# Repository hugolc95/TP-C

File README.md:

#Hugo LE COZ 3DN 

USART2 mode asynchrone baud rate = 115200 bit/s

Clock configuration = 32 MHz 

## **1.2 Le microcontrôleur sous KiCAD**

13. PB9 à la masse permet de choisir la selection du modes de boot

14. Le role de L1, C5, C7 est un filtre passe bas du second ordre qui permet de supprimer les parasites de l'alimentation

## **1.3 Le reste du schémas**

3. On peut retrouver sur la première page la valeur que doit avoir au minimum Cin et Cout de 0.47uF mais sur la page 3 on nous indique une valeur typique de 1uF
4.
5. Valeur condensateur page 25
6. CS => Chip Select est activée à l'état bas et permettre ainsi l'établissement de la communication SPI
7. LDAC => (Load DAC) Lorsque cette entrée est à 0, elle provoque un changement de la tension de sortie et lorsque la broche LDAC est activée, les valeurs enregistrées dans le registre de mise à jour sont chargées simultanément dans tous les DAC associés. Cela permet d'assurer une mise à jour cohérente et synchrone des sorties analogiques.
8. MISO => la broche MISO n'existe pas dans le DAC
9.
10. cela se trouve dans la documentation du STLink page 26

## **3.1 Activation des LL drivers**

2. 
3.
4. __STATIC_INLINE est un modificateur de type de fonction qui indique au compilateur de traiter la fonction comme étant statique et en ligne.
5.

##3.2 LED simple

2. La valeur du prescaler est de 63

## 3.3 LED avec timer

1- On active le TIM21 

2- Pour qu'il y est des interruption toutes les milli-secondes
On met 16000 pour le prescaler et 1000 pour l'AutoReloadRegister (ARR)

6- La routine de service d’interruption se trouve dans le fichier stm3210xx_it.c

7- 

## 3.4 UART

code photo telephone

5- il manque le **&**, il faut donnée une adresse car la déclaration de SerialTransmit(**&** ch, 1); le premier parametre est un pointeur

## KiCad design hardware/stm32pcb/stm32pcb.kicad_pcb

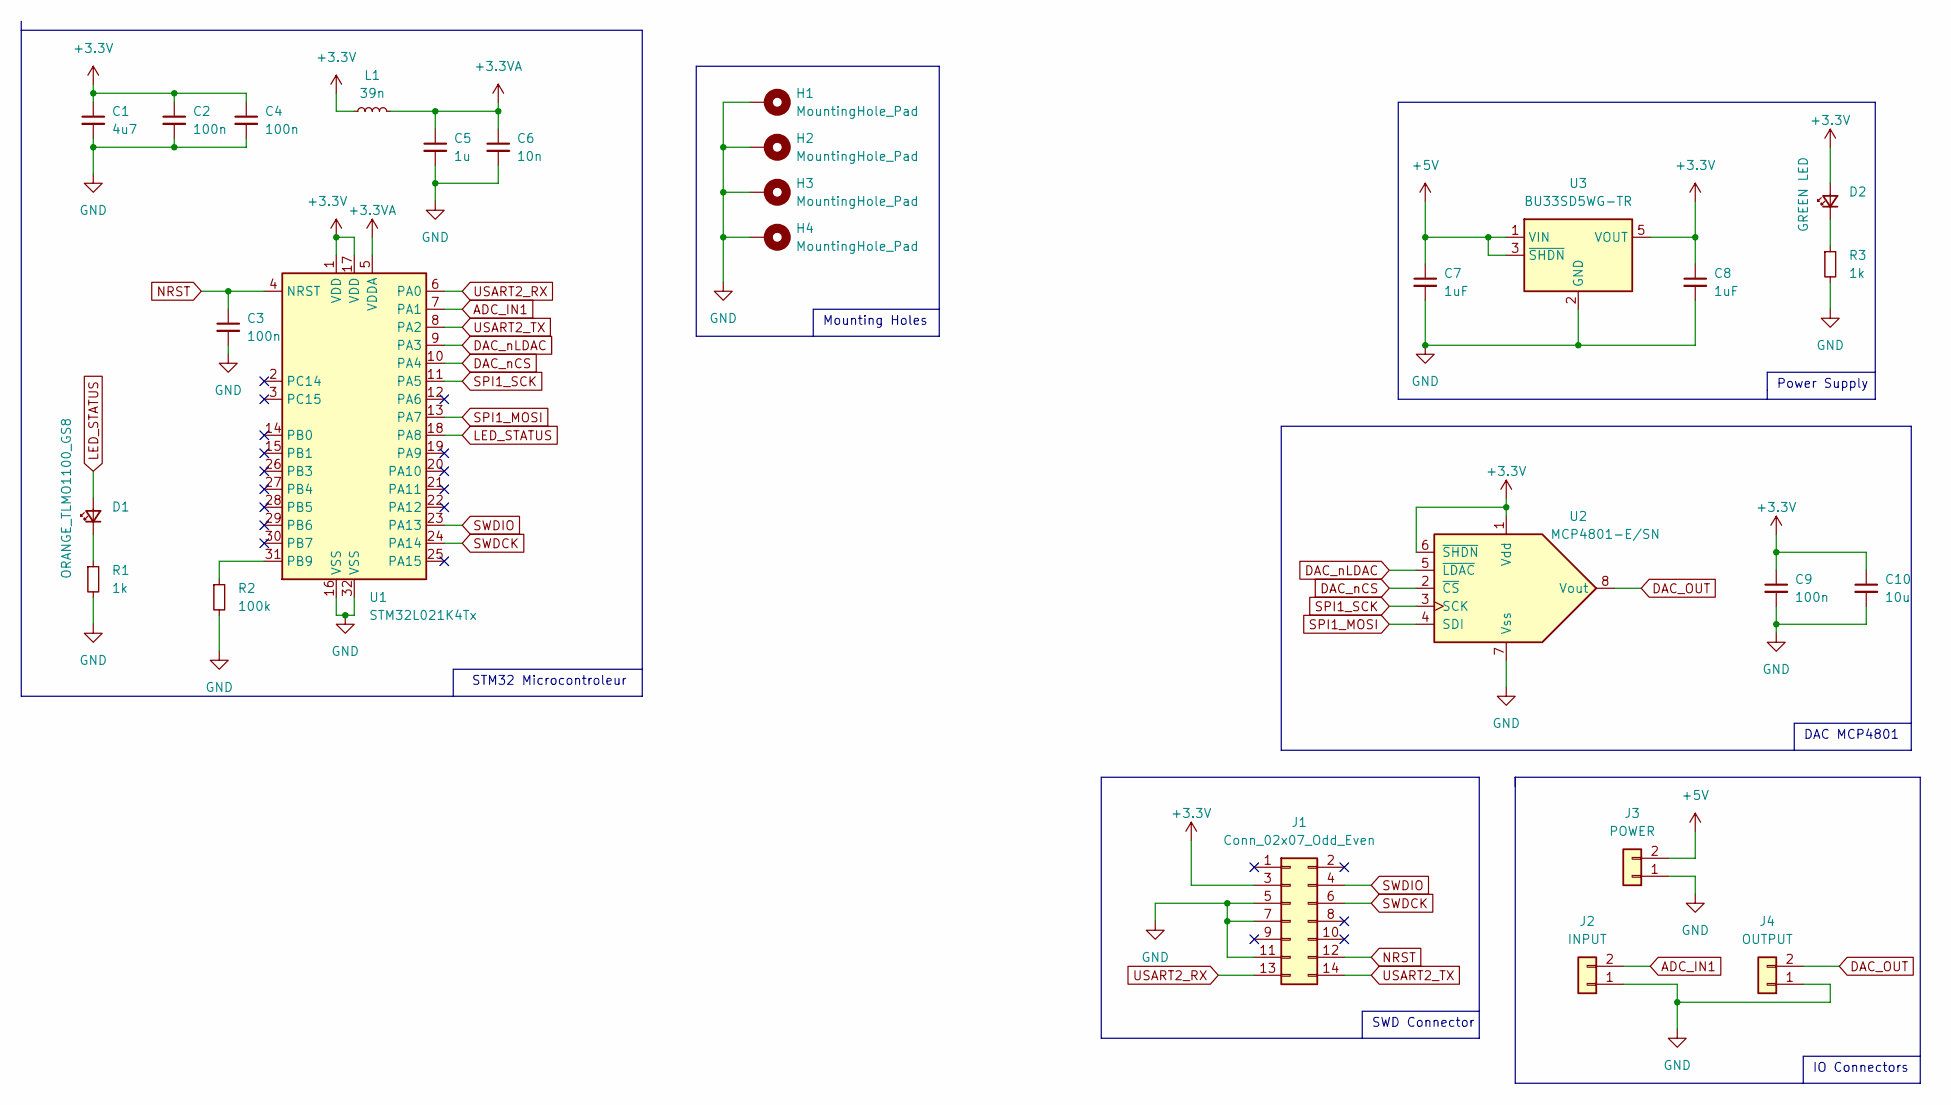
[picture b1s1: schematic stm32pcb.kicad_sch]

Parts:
C1: 4u7; C_0805_2012Metric_Pad1.18x1.45mm_HandSolder
C2, C3, C4, C9: 100n; C_0805_2012Metric_Pad1.18x1.45mm_HandSolder
C5: 1u; C_0805_2012Metric_Pad1.18x1.45mm_HandSolder
C6: 10n; C_0805_2012Metric_Pad1.18x1.45mm_HandSolder
C7, C8: 1uF; C_0805_2012Metric
C10: 10u; C_0805_2012Metric
D1: ORANGE_TLMO1100_GS8; LED_0603_1608Metric_Pad1.05x0.95mm_HandSolder
D2: GREEN LED; LED_0603_1608Metric_Pad1.05x0.95mm_HandSolder
H1, H2, H3, H4: MountingHole_Pad; MountingHole_3.2mm_M3_Pad
J1: Conn_02x07_Odd_Even; PinHeader_2x07_P1.27mm_Vertical_SMD
J2: INPUT; JST_XH_B2B-XH-A_1x02_P2.50mm_Vertical
J3: POWER; JST_XH_B2B-XH-A_1x02_P2.50mm_Vertical
J4: OUTPUT; JST_XH_B2B-XH-A_1x02_P2.50mm_Vertical
L1: 39n; L_0805_2012Metric_Pad1.05x1.20mm_HandSolder
R1, R3: 1k; R_0805_2012Metric_Pad1.20x1.40mm_HandSolder
R2: 100k; R_0805_2012Metric_Pad1.20x1.40mm_HandSolder
U1: STM32L021K4Tx; LQFP-32_7x7mm_P0.8mm
U2: MCP4801-E/SN; SOIC-8_3.9x4.9mm_P1.27mm
U3: BU33SD5WG-TR; SOT-23-5

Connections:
+3.3V: C1.1, C2.1, C4.1, C8.1, C9.1, C10.1, D2.2 (A), J1.3, L1.1, U1.1 (VDD), U1.17 (VDD), U2.1 (Vdd), U2.6 (~SHDN), U3.5 (VOUT)
+3.3VA: C5.1, C6.1, L1.2, U1.5 (VDDA)
+5V: C7.1, J3.2, U3.1 (VIN), U3.3 (~SHDN)
ADC_IN1: J2.2, U1.7 (PA1)
DAC_OUT: J4.2, U2.8 (Vout)
DAC_nCS: U1.10 (PA4), U2.2 (~CS)
DAC_nLDAC: U1.9 (PA3), U2.5 (~LDAC)
GND: C1.2, C2.2, C3.2, C4.2, C5.2, C6.2, C7.2, C8.2, C9.2, C10.2, H1.1, H2.1, H3.1, H4.1, J1.5, J1.7, J1.11, J2.1, J3.1, J4.1, R1.2, R2.2, R3.2, U1.16 (VSS), U1.32 (VSS), U2.7 (Vss), U3.2 (GND)
LED_STATUS: D1.2 (A), U1.18 (PA8)
NRST: C3.1, J1.12, U1.4 (NRST)
unnamed: D1.1 (K), R1.1
unnamed: D2.1 (K), R3.1
unnamed: R2.1, U1.31 (PB9)
SPI1_MOSI: U1.13 (PA7), U2.4 (SDI)
SPI1_SCK: U1.11 (PA5), U2.3 (SCK)
SWDCK: J1.6, U1.24 (PA14)
SWDIO: J1.4, U1.23 (PA13)
USART2_RX: J1.13, U1.6 (PA0)
USART2_TX: J1.14, U1.8 (PA2)

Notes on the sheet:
IO Connectors
STM32 Microcontroleur
DAC MCP4801
SWD Connector
Mounting Holes
Power Supply

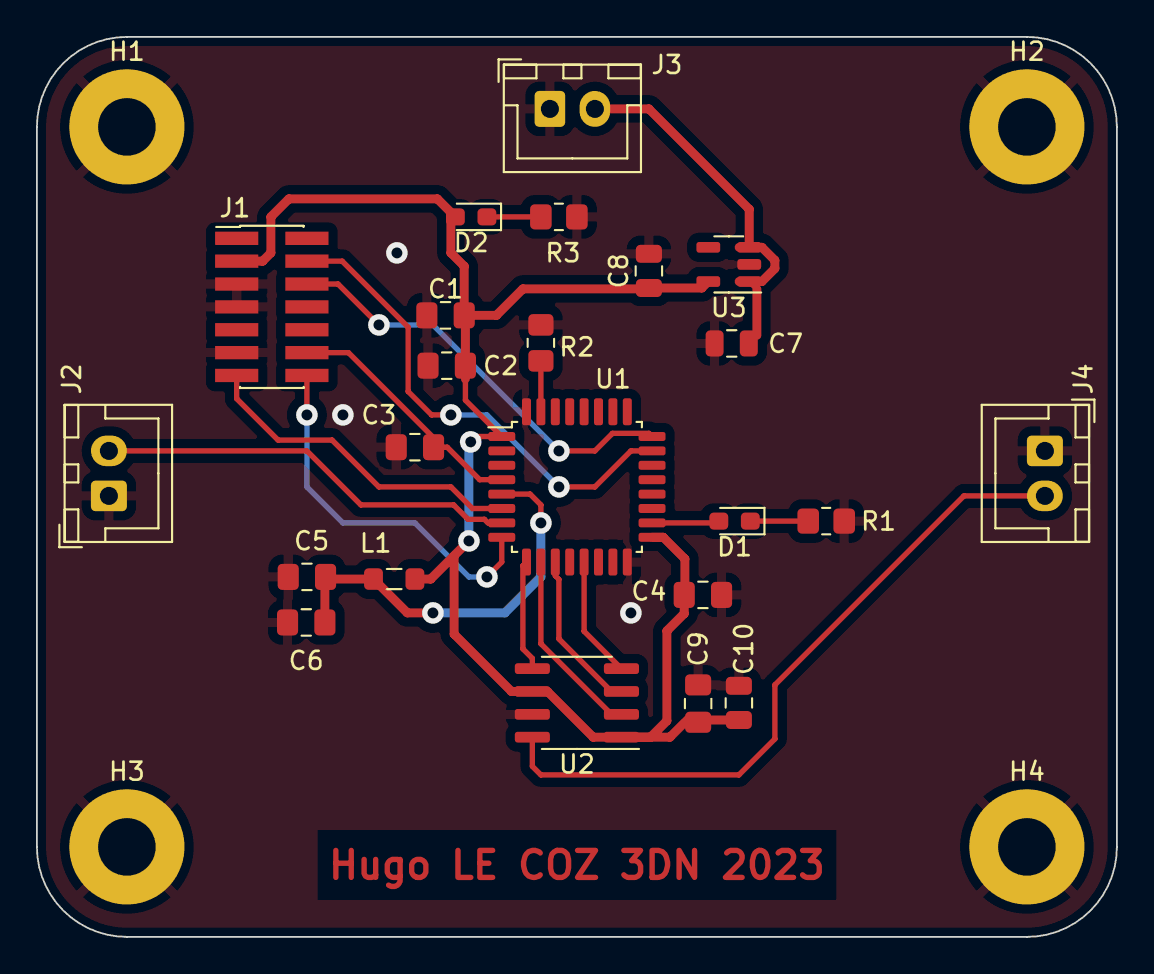
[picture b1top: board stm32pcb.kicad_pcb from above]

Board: 2 copper layers, 60.0 x 50.0 mm, 27 parts (0 on the bottom side), 19 nets.

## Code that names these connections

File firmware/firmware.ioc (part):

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Mcu.Name=STM32L021K4Tx
Mcu.Package=LQFP32
Mcu.UserName=STM32L021K4Tx
PA0-CK_IN.Mode=Asynchronous
PA0-CK_IN.Signal=USART2_RX
PA1.Mode=IN1
PA1.Signal=ADC_IN1
PA13.Mode=Serial_Wire
PA13.Signal=SYS_SWDIO
PA14.Mode=Serial_Wire
PA14.Signal=SYS_SWCLK
PA2.Mode=Asynchronous
PA2.Signal=USART2_TX
PA3.GPIOParameters=GPIO_Label
PA3.GPIO_Label=DAC_nLDAC
PA3.Signal=GPIO_Output
PA4.GPIOParameters=GPIO_Label
PA4.GPIO_Label=DAC_nCS
PA4.Signal=GPIO_Output
PA5.Mode=Full_Duplex_Master
PA5.Signal=SPI1_SCK
PA6.Mode=Full_Duplex_Master
PA6.Signal=SPI1_MISO
PA7.Mode=Full_Duplex_Master
PA7.Signal=SPI1_MOSI
PA8.Signal=S_TIM2_CH1
RCC.HSE_VALUE=8000000
RCC.SYSCLKFreq_VALUE=32000000
RCC.SYSCLKSource=RCC_SYSCLKSOURCE_PLLCLK
board=custom

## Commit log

2023-02-15 ajout fichier test
2023-02-15 Ajout des datasheets des composants
2023-02-15 add README.md
2023-02-15 sauvegarde dans le dossier firmware
2023-02-15 Cablage schemas KiCad
2023-02-15 config stm32
2023-02-15 add Empreintes
2023-02-16 Routage fini
2023-03-10 code Led Simple OK
2023-03-10 Ajout image et timeBase
2023-03-10 timer et uart
2023-03-12 format
2023-03-16 add picture and reponse
2023-03-16 resize picture
